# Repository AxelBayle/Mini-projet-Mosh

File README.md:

# Mini-projet-Mosh

## Projet Capteur de Gaz sur Arduino
### Introduction
Dans le cadre de l'UF MOSH (Microcontroleurs and Open Source Hardware) de la 5e année ISS, nous avons conçu un système de captation de certains gaz (gaz naturel, monoxyde de carbone, gaz de charbon) et la transmission des informations capteur via Lora pour pouvoir les visualiser en ligne à distance et être alerté si un certain seuil est dépassé. Deux capteurs ont été utilisés afin de réaliser ce système de détection. Le premier est un capteur commercial existant, le deuxième a été créé par nos soins et fera l'objet d'une partie dédiée quant à son conception et son fonctionnement.
Dans ce dossier se trouve un dossier avec le code arduino,le projet Kicad pour le shield et un dossier pour le projet Kicad de la carte du capteur de gaz.

### Code arduino embarqué
#### Concept principal
L'objectif de notre système est de définir à travers les informations reçues par un capteur de gaz une alerte et une visualisation en temps réelle du niveau de gaz capté à travers une plateforme web dédiée. Les données capteur sont transmises à la carte Arduino puis mises en forme avant d'être envoyées via Lora à la plateforme TheThingsNetwork. Elles transitent ensuite vers un serveur dédié où la plateforme NodeRed permet de les mettre en forme et de les afficher de façon lisible.

#### Architecture
Le code embarqué sur l'Arduino est structuré en 4 grandes parties :
* Import des librairies et définition des constantes
* Définitions des callback des interruptions
* le void setup() où les GPIO sont initialisés ainsi que les interruptions et uù l'on effectue le Reset de la puce Lora
* le void loop(), la partie exécutive du code où l'on récupère les données du capteur avant de les mettre forme et de les envoyer via l'antenne Lora

#### Capteurs et Actionneurs

Dans cette version nous utilisons le capteur de gaz commercial MQ5 pour Arduino. En plus du capteur en lui même le système comporte une LED rouge pour l'alerte en cas de dépassement du seuil défini. Il y a aussi un montage servant de déclencheur pour l'interruption dans le cas où la tension mesurée par le capteur est plus élevée que le seuil.

#### Librairies utilisées
Nous utilisons 2 librairires en plus de ce qui est déjà inclus dans l'environnement d'Arduino.
* SoftwareSerial.h : permet d'émuler un port série sur un port  GPIO classique. Cette librairie est nécessaire pour utiliser le dongle Lora et nous permet d'avoir deux bus séries. Le premier pour la communication avec la puce Lora et le deuxième pour le débugage et l'affichage sur le moniteur.
* TheThingsNetwork.h : permet de transférer des données en utilisant le protocole Lora et de les faire transiter via la plateforme pour IoT thethingsnetwork.org

### Réception des données sur TheThingsNetwork
La mise en forme des données sur TTN a été pensée pour être le plus simple possible. La valeur retourné par le capteur est convertie en valeur binaire sur deux octets puis envoyée directement. Ainsi on envoi le moins de données possible car il n'y a que la valeur interessante qui est envoyé.

### Mise en forme des données avec NodeRed
La première étape sur NodeRed est d'extraire la valeur du message. Pour cela il suffit de récupérer la valeur dans le champs payload. Ensuite on peut afficher directement cette valeur sur une interface de type graphique ou jauge. Mais la valeur est une valeur comprise en 0 et 1024 et n'est pas très significative, c'est pour ça que nous avons aussi traduit cette valeur en tension ( formule de conversion ADC ) pour l'afficher dans une jauge séparée. Cet affichage est beaucoup plus parlant car la valeur affichée et la tension du capteur.

### Conclusion & Résultats obtenus
Le premier constat de notre solution est une importante consommation de courant, cependant en investigeant et en analysant les différentes parties on a compris que cela venait du capteur car celui-ci a besoin de travailler à haute température pour avoir une meilleure réactivité aux gaz, c'est pourquoi nous n'avons pas éssayé de réduire le courant consommé par notre code et notre montage (capteur excepté) car cela représente moins de 1/5 de la consommation totale.

Quant aux résultats obtenus, nous sommes très satisfaits car le système répond vite à la présence de gaz, la gestion des interruptions est précise grâce au filtre rajouté, enfin le dahsboard est clair et sobre mais fournit toutes les infos voulues.
## Conception d'un capteur de gaz à nano-particules
Par la suite nous allons fabriquer un capteur de gaz à nano-particules, pour l'introduire sur notre carte on a choisi de faire une carte séparée qui va être en charge de l'amplification du signal et cette carte sera connectée au shield via une liaison 4fils groove.

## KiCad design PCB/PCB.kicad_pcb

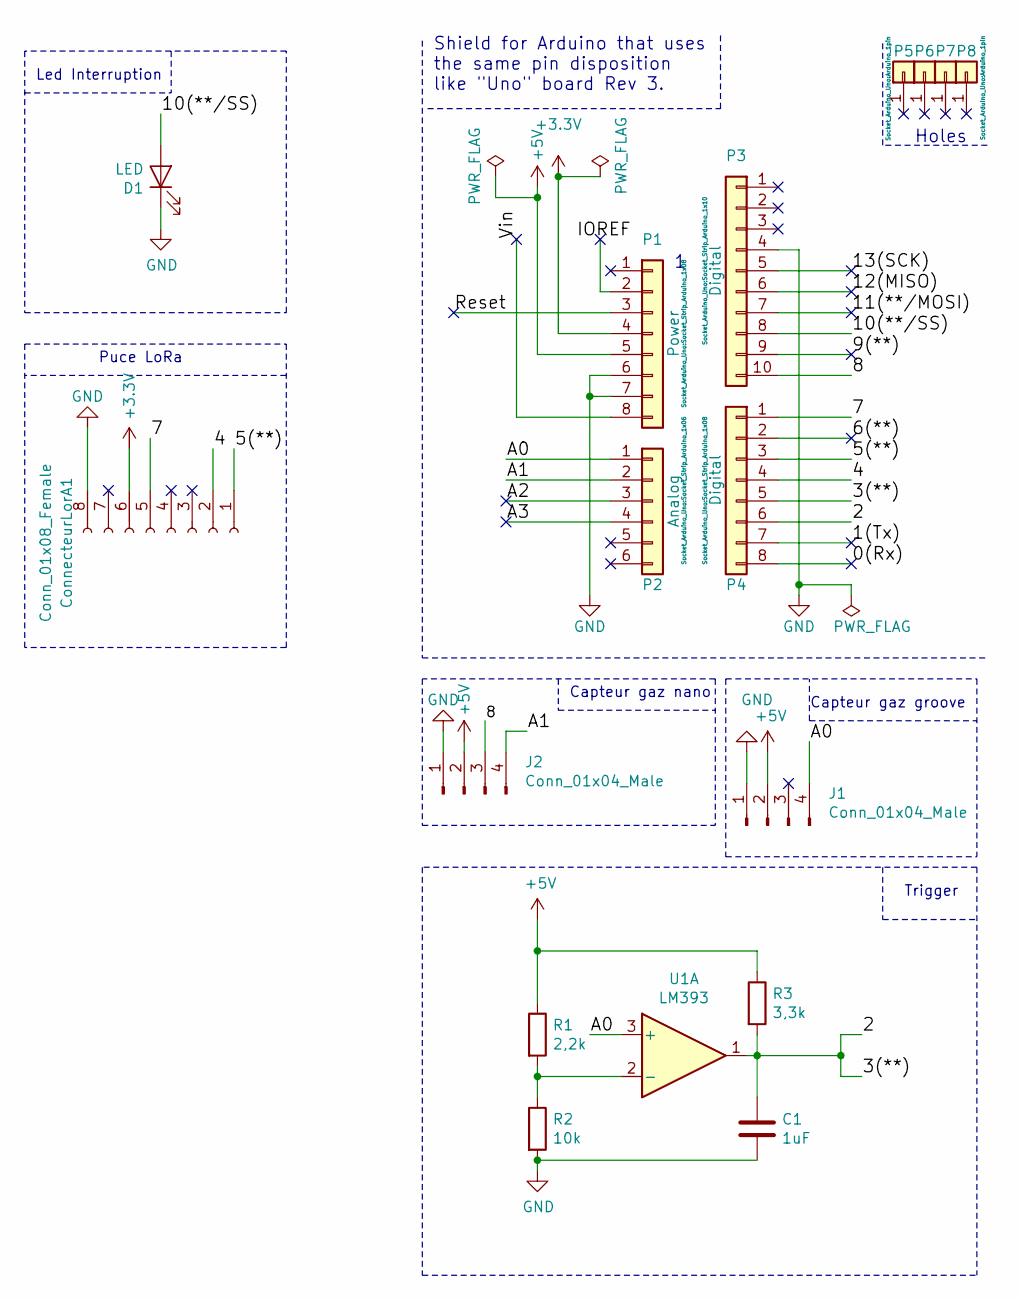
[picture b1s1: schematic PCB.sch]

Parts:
C1: 1uF; C_Rect_L4.0mm_W2.5mm_P2.50mm
ConnecteurLorA1: Conn_01x08_Female; PinHeader_1x08_P2.54mm_Vertical
D1: LED; LED_D5.0mm
J1, J2: Conn_01x04_Male; PinSocket_1x04_P2.54mm_Vertical
P1: Power; Socket_Strip_Arduino_1x08
P2: Analog; Socket_Strip_Arduino_1x06
P3: Digital; Socket_Strip_Arduino_1x10
P4: Digital; Socket_Strip_Arduino_1x08
P5, P6, P7, P8: CONN_01X01; Arduino_1pin
R1: 2,2k; R_Axial_DIN0204_L3.6mm_D1.6mm_P7.62mm_Horizontal
R2: 10k; R_Axial_DIN0204_L3.6mm_D1.6mm_P7.62mm_Horizontal
R3: 3,3k; R_Axial_DIN0204_L3.6mm_D1.6mm_P7.62mm_Horizontal
U1: LM393; DIP-8_W7.62mm

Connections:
+3V3: ConnecteurLorA1.6, P1.4
+5V: J1.2, J2.2, P1.5, R1.1, R3.1
/0(Rx): P4.8
/1(Tx): P4.7
/2: C1.1, P4.5, P4.6, R3.2, U1.1
/4: ConnecteurLorA1.2, P4.4
/5(**): ConnecteurLorA1.1, P4.3
/6(**): P4.2
/7: ConnecteurLorA1.5, P4.1
/8: J2.3, P3.10
/9(**): P3.9
/10(**/SS): D1.2 (A), P3.8
/11(**/MOSI): P3.7
/12(MISO): P3.6
/13(SCK): P3.5
/A0: J1.4, P2.1, U1.3 (+)
/A1: J2.4, P2.2
/A2: P2.3
/A3: P2.4
/Reset: P1.3
/Vin: P1.8
GND: C1.2, ConnecteurLorA1.8, D1.1 (K), J1.1, J2.1, P1.6, P1.7, P3.4, R2.2
unnamed: R1.2, R2.1, U1.2 (-)

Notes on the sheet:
Holes
Shield for Arduino that uses the same pin disposition like "Uno" board Rev 3.
Led Interruption
Puce LoRa
Capteur gaz groove
Capteur gaz nano
Trigger

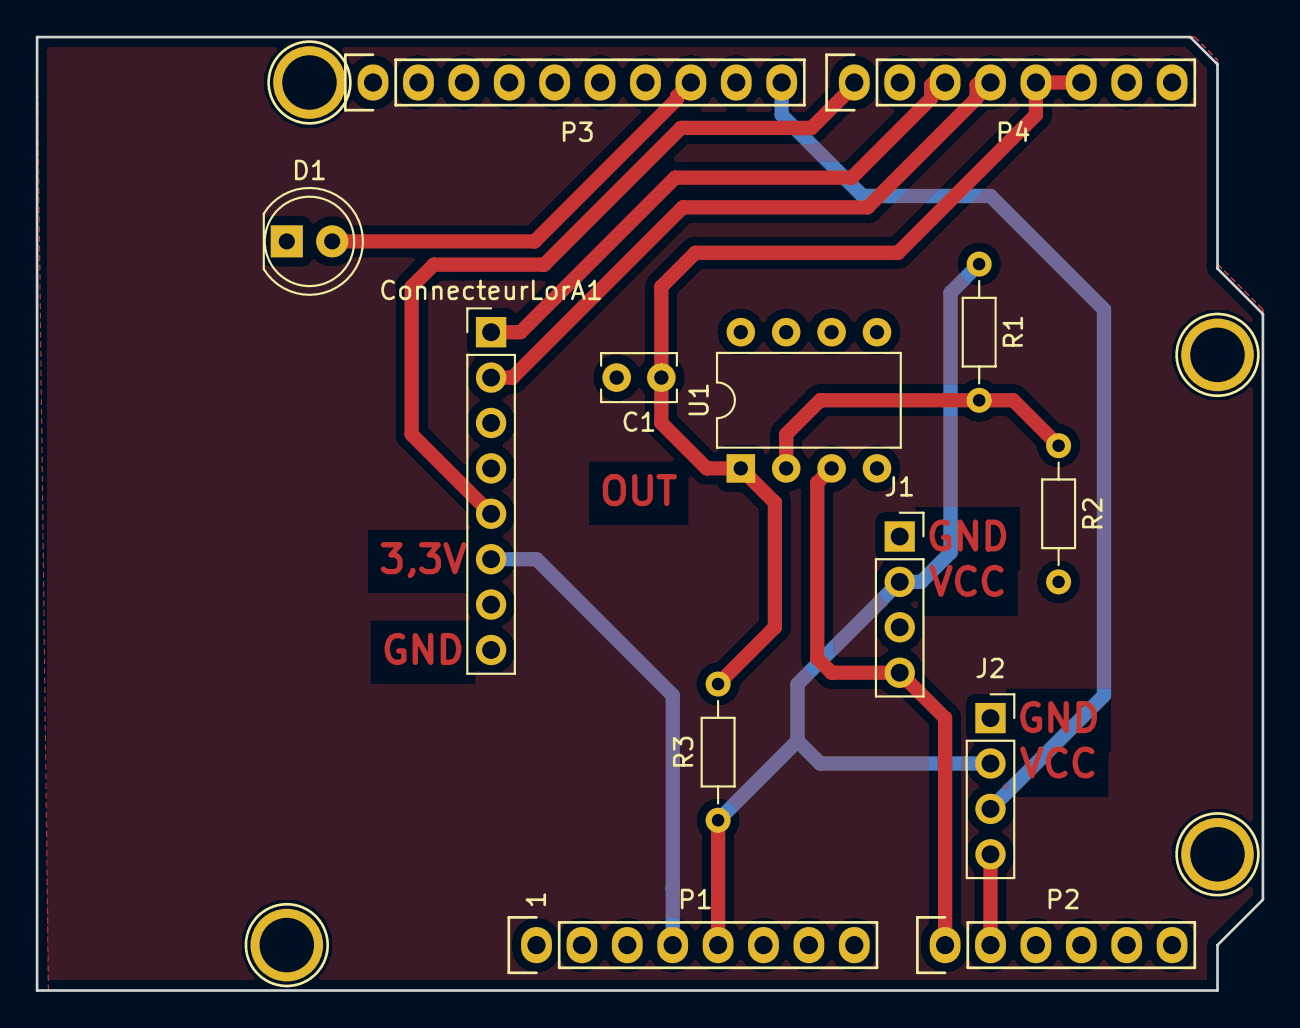
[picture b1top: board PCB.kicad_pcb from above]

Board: 2 copper layers, 68.6 x 53.3 mm, 17 parts (0 on the bottom side), 12 nets.

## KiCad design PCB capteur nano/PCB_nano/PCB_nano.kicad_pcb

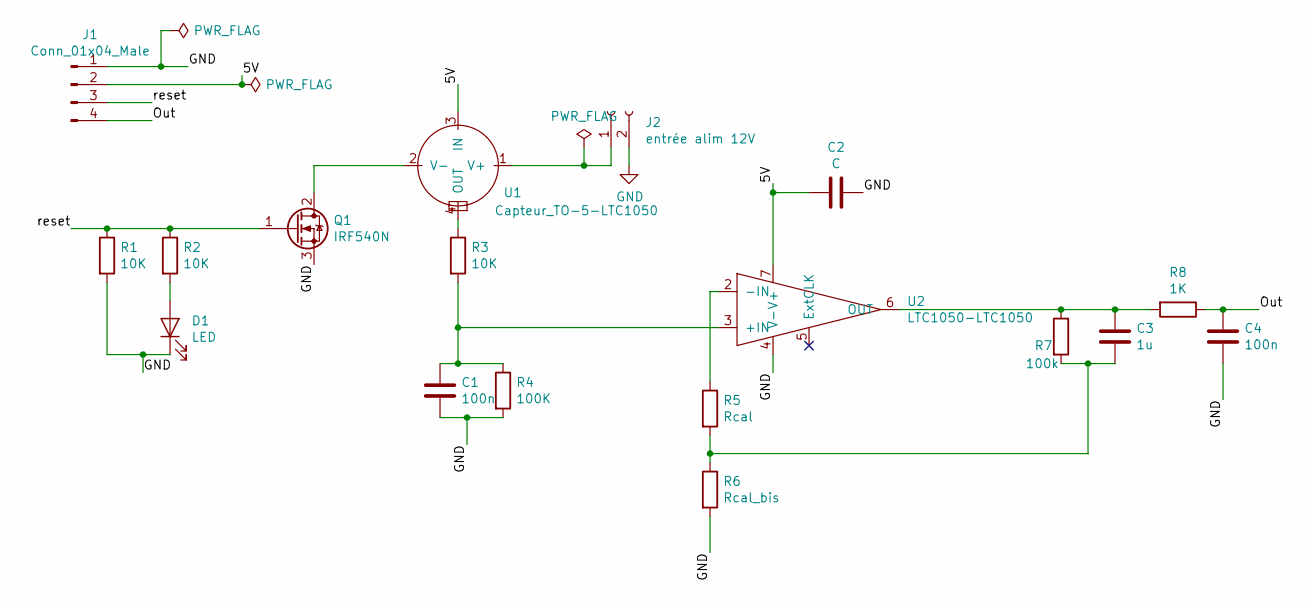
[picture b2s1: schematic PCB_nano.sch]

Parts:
C1, C4: 100n; C_Rect_L4.0mm_W2.5mm_P2.50mm
C2: C; C_Rect_L4.0mm_W2.5mm_P2.50mm
C3: 1u; C_Rect_L4.0mm_W2.5mm_P2.50mm
D1: LED; LED_D1.8mm_W3.3mm_H2.4mm
J1: Conn_01x04_Male; NS-Tech_Grove_1x04_P2mm_Vertical
J2: entrée alim 12V; PinSocket_1x02_P2.54mm_Vertical
Q1: IRF540N; TO-220-3_Vertical
R1, R2, R3: 10K; R_Axial_DIN0204_L3.6mm_D1.6mm_P5.08mm_Horizontal
R4: 100K; R_Axial_DIN0204_L3.6mm_D1.6mm_P5.08mm_Horizontal
R5: Rcal; R_Axial_DIN0204_L3.6mm_D1.6mm_P5.08mm_Horizontal
R6: Rcal_bis; R_Axial_DIN0204_L3.6mm_D1.6mm_P5.08mm_Horizontal
R7: 100k; R_Axial_DIN0204_L3.6mm_D1.6mm_P5.08mm_Horizontal
R8: 1K; R_Axial_DIN0204_L3.6mm_D1.6mm_P5.08mm_Horizontal
U1: Capteur_TO-5-LTC1050; TO-5-4
U2: LTC1050-LTC1050; DIP-8_W7.62mm_Socket_LongPads

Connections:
/5V: C2.2, J1.2, U1.3 (IN), U2.7 (V+)
/Out: C4.1, J1.4, R8.1
/reset: J1.3, Q1.1 (G), R1.1, R2.1
GND: C1.2, C2.1, C4.2, D1.1 (K), J1.1, J2.2, Q1.3 (S), R1.2, R4.2, R6.2, U2.4 (V-)
unnamed: C1.1, R3.2, R4.1, U2.3 (+IN)
unnamed: C3.1, R7.1, R8.2, U2.6 (OUT)
unnamed: C3.2, R5.2, R6.1, R7.2
unnamed: D1.2 (A), R2.2
unnamed: J2.1, U1.1 (V+)
unnamed: Q1.2 (D), U1.2 (V-)
unnamed: R3.1, U1.4 (OUT)
unnamed: R5.1, U2.2 (-IN)

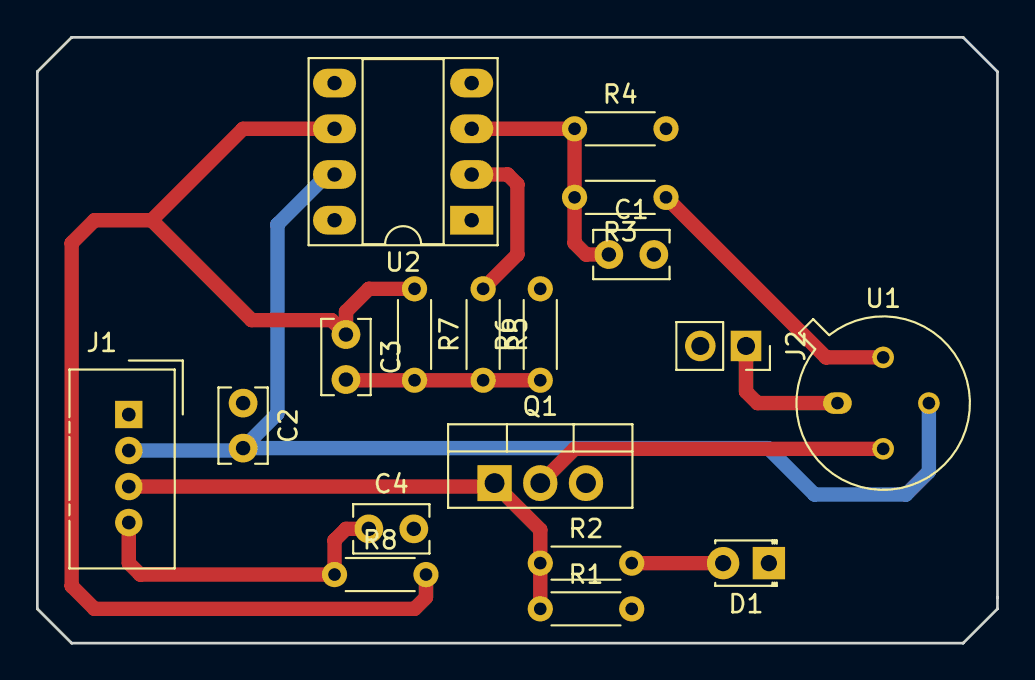
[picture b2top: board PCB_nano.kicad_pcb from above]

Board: 2 copper layers, 53.3 x 33.7 mm, 18 parts (0 on the bottom side), 12 nets.

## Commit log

2018-10-01 premier commit
2018-10-02 V1 : Lora + IT + données capteur de gaz
2018-10-08 mise en forme trames
2018-10-29 Ajout carte PCB
2018-11-05 ajout screen
2018-11-06 ajout pcb capteur nano et maj pcb shield
2018-11-12 Photo board complète
